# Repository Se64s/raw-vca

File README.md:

# raw-vca

Eurorack VCA module based in EDU DIY VCA from erica synths and Moritz Klein.

# About the project

This is the second module of the series 'RAW'.

The RAW concept is my way to ease access to the modular world, reducing the cost of the modules to the minimum and removing all unnecessary parts without scarify functionality.

In this case, I took the design of Moritz as a base for this VCA.

# Module overview

## Inputs

- 3 independent VCA.
- offset potentiometer per VCA.

## Output

### Square wave

### Triangle wave

### AR envelope

### Audio rate

## Calibration

Use the same procedure described for the Moritz VCA. Synth Diy Guy has an awesome video with the entire process.

- [Calibration](https://www.youtube.com/watch?v=xxr5fT-E7m0)

# Acknowledgments

All design and guts of this module were done by Moritz Klein so I recommend visiting his awesome videos to get a precise idea of how this module works.

- [mki x es.EDU](https://www.ericasynths.lv/news/edu-diy-vca/)

# Contact

Any feedback is welcome!
- Sebastián Del Moral - sebmorgal@gmail.com

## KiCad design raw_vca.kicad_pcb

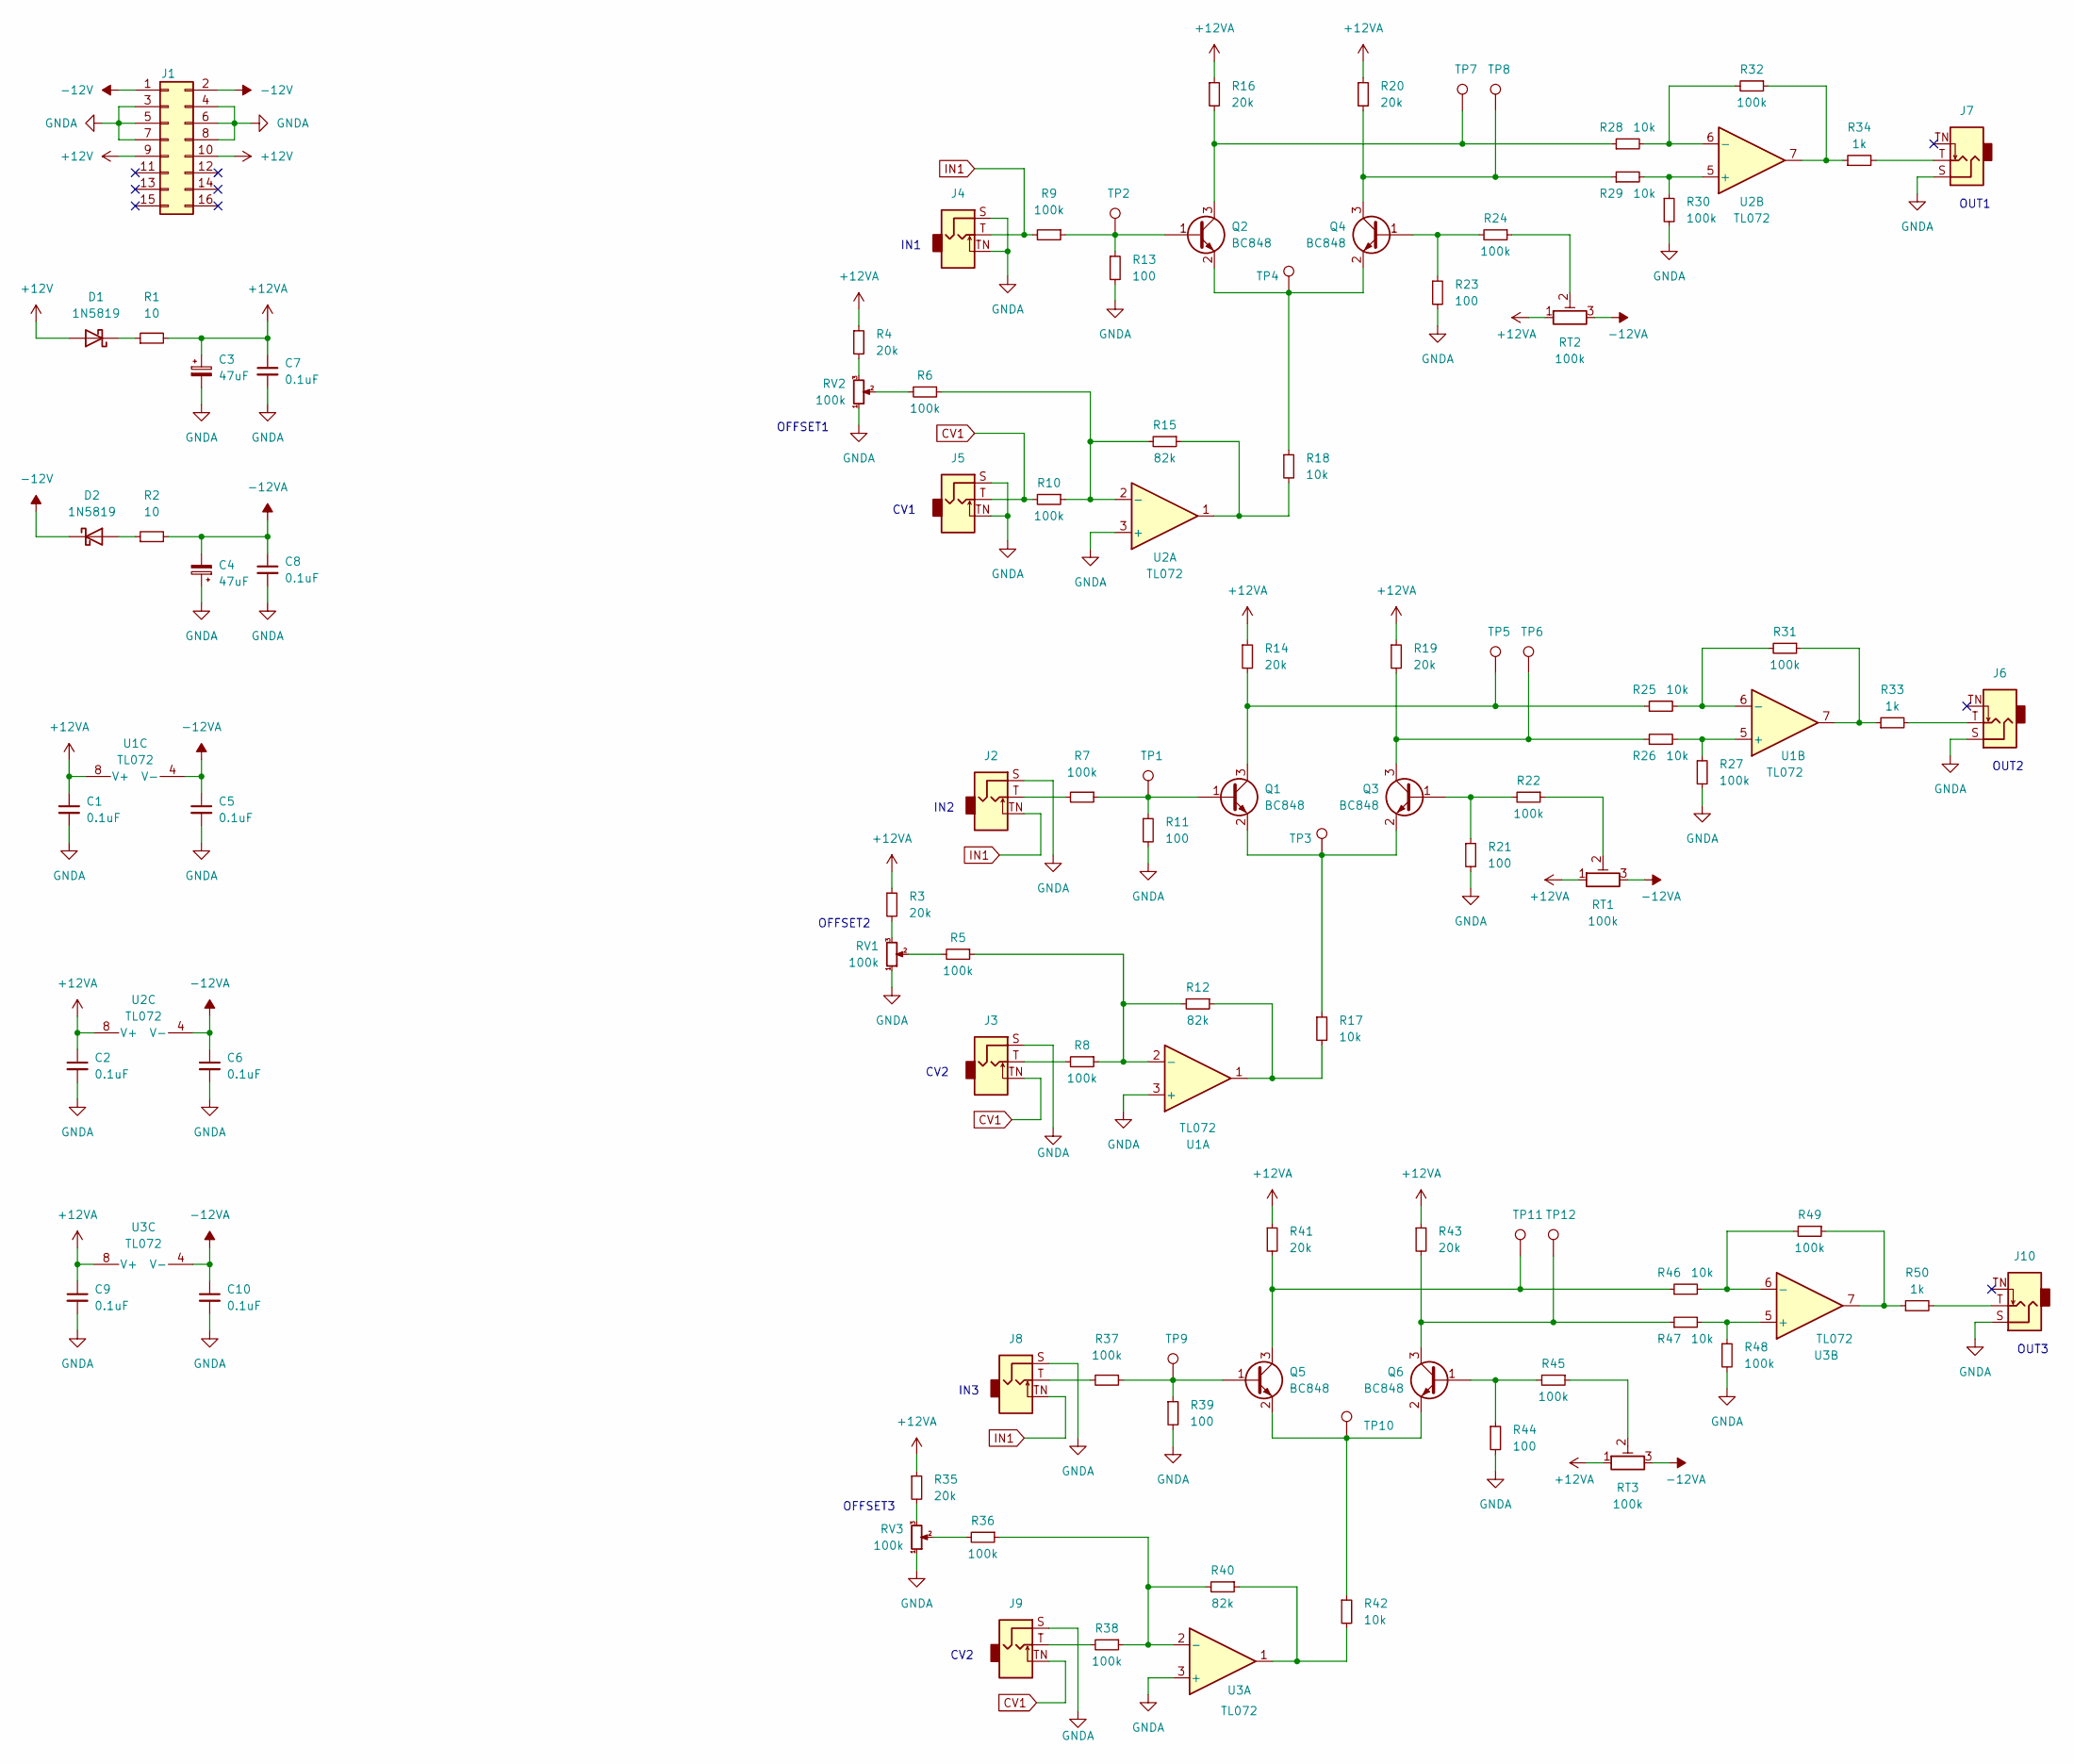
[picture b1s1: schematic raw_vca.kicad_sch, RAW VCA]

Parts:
C1, C2, C5, C6, C7, C8, C9, C10: 0.1uF; C_0603_1608Metric_Pad1.08x0.95mm_HandSolder
C3, C4: 47uF; CP_Elec_6.3x5.4
D1, D2: 1N5819; D_SOD-123
J1: Conn_02x08_Odd_Even; PinHeader_2x08_P2.54mm_Vertical_SMD
J2, J3, J4, J5, J6, J7, J8, J9, J10: AudioJack2_SwitchT; Jack_3.5mm_QingPu_WQP-PJ398SM_Vertical_CircularHoles
Q1, Q2, Q3, Q4, Q5, Q6: BC848; SOT-23
R1, R2: 10; R_0805_2012Metric_Pad1.20x1.40mm_HandSolder
R3, R4, R14, R16, R19, R20, R35, R41, R43: 20k; R_0603_1608Metric_Pad0.98x0.95mm_HandSolder
R5, R6, R7, R8, R9, R10, R22, R24, R27, R30, R31, R32, R36, R37, R38, R45, R48, R49: 100k; R_0603_1608Metric_Pad0.98x0.95mm_HandSolder
R11, R13, R21, R23, R39, R44: 100; R_0603_1608Metric_Pad0.98x0.95mm_HandSolder
R12, R15, R40: 82k; R_0603_1608Metric_Pad0.98x0.95mm_HandSolder
R17, R18, R25, R26, R28, R29, R42, R46, R47: 10k; R_0603_1608Metric_Pad0.98x0.95mm_HandSolder
R33, R34, R50: 1k; R_0603_1608Metric_Pad0.98x0.95mm_HandSolder
RT1, RT2, RT3: 100k; Potentiometer_Bourns_3296W_Vertical
RV1, RV2, RV3: 100k; Potentiometer_Alpha_RD901F-40-00D_Single_Vertical
TP1, TP2, TP3, TP4, TP5, TP6, TP7, TP8, TP9, TP10, TP11, TP12: TestPoint; TestPoint_Pad_D1.5mm
U1, U2, U3: TL072; SOIC-8_3.9x4.9mm_P1.27mm

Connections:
+12V: D1.2 (A), J1.9, J1.10
+12VA: C1.1, C2.1, C3.1, C7.1, C9.1, R1.2, R3.1, R4.1, R14.1, R16.1, R19.1, R20.1, R35.1, R41.1, R43.1, RT1.1, RT2.1, RT3.1, U1.8 (V+), U2.8 (V+), U3.8 (V+)
-12V: D2.1 (K), J1.1, J1.2
-12VA: C4.2, C5.1, C6.1, C8.1, C10.1, R2.2, RT1.3, RT2.3, RT3.3, U1.4 (V-), U2.4 (V-), U3.4 (V-)
CV1: J3.TN, J5.T, J9.TN, R10.2
GNDA: C1.2, C2.2, C3.2, C4.1, C5.2, C6.2, C7.2, C8.2, C9.2, C10.2, J1.3, J1.4, J1.5, J1.6, J1.7, J1.8, J2.S, J3.S, J4.S, J4.TN, J5.S, J5.TN, J6.S, J7.S, J8.S, J9.S, J10.S, R11.2, R13.2, R21.2, R23.2, R27.2, R30.2, R39.2, R44.2, R48.2, RV1.1, RV2.1, RV3.1, U1.3 (+), U2.3 (+), U3.3 (+)
IN1: J2.TN, J4.T, J8.TN, R9.2
unnamed: D1.1 (K), R1.1
unnamed: D2.2 (A), R2.1
unnamed: J2.T, R7.2
unnamed: J3.T, R8.2
unnamed: J6.T, R33.2
unnamed: J7.T, R34.2
unnamed: J8.T, R37.2
unnamed: J9.T, R38.2
unnamed: J10.T, R50.2
unnamed: Q1.1 (B), R7.1, R11.1, TP1.1
unnamed: Q1.2 (E), Q3.2 (E), R17.1, TP3.1
unnamed: Q1.3 (C), R14.2, R25.1, TP5.1
unnamed: Q2.1 (B), R9.1, R13.1, TP2.1
unnamed: Q2.2 (E), Q4.2 (E), R18.1, TP4.1
unnamed: Q2.3 (C), R16.2, R28.1, TP7.1
unnamed: Q3.1 (B), R21.1, R22.2
unnamed: Q3.3 (C), R19.2, R26.1, TP6.1
unnamed: Q4.1 (B), R23.1, R24.2
unnamed: Q4.3 (C), R20.2, R29.1, TP8.1
unnamed: Q5.1 (B), R37.1, R39.1, TP9.1
unnamed: Q5.2 (E), Q6.2 (E), R42.1, TP10.1
unnamed: Q5.3 (C), R41.2, R46.1, TP11.1
unnamed: Q6.1 (B), R44.1, R45.2
unnamed: Q6.3 (C), R43.2, R47.1, TP12.1
unnamed: R3.2, RV1.3
unnamed: R4.2, RV2.3
unnamed: R5.2, RV1.2
unnamed: R6.2, RV2.2
unnamed: R6.1, R10.1, R15.2, U2.2 (-)
unnamed: R12.1, R17.2, U1.1
unnamed: R5.1, R8.1, R12.2, U1.2 (-)
unnamed: R15.1, R18.2, U2.1
unnamed: R22.1, RT1.2
unnamed: R24.1, RT2.2
unnamed: R25.2, R31.2, U1.6 (-)
unnamed: R26.2, R27.1, U1.5 (+)
unnamed: R28.2, R32.2, U2.6 (-)
unnamed: R29.2, R30.1, U2.5 (+)
unnamed: R31.1, R33.1, U1.7
unnamed: R32.1, R34.1, U2.7
unnamed: R35.2, RV3.3
unnamed: R36.1, R38.1, R40.2, U3.2 (-)
unnamed: R36.2, RV3.2
unnamed: R40.1, R42.2, U3.1
unnamed: R45.1, RT3.2
unnamed: R46.2, R49.2, U3.6 (-)
unnamed: R47.2, R48.1, U3.5 (+)
unnamed: R49.1, R50.1, U3.7

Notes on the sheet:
OUT3
IN3
IN1
CV1
CV2
OFFSET3
OUT1
OFFSET1
IN2
OUT2
OFFSET2

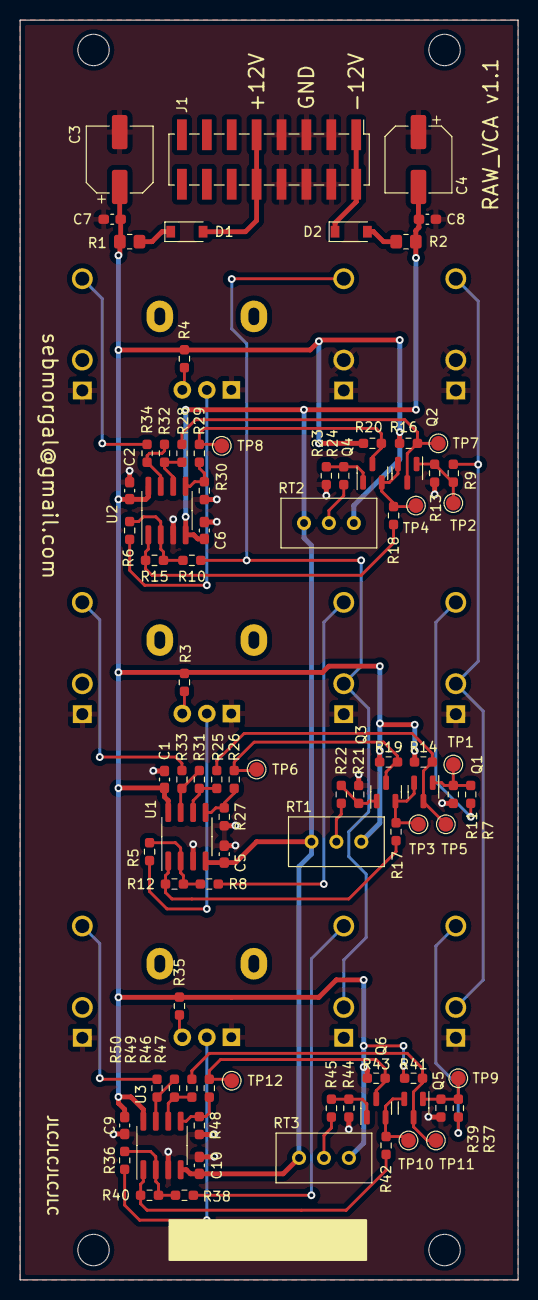
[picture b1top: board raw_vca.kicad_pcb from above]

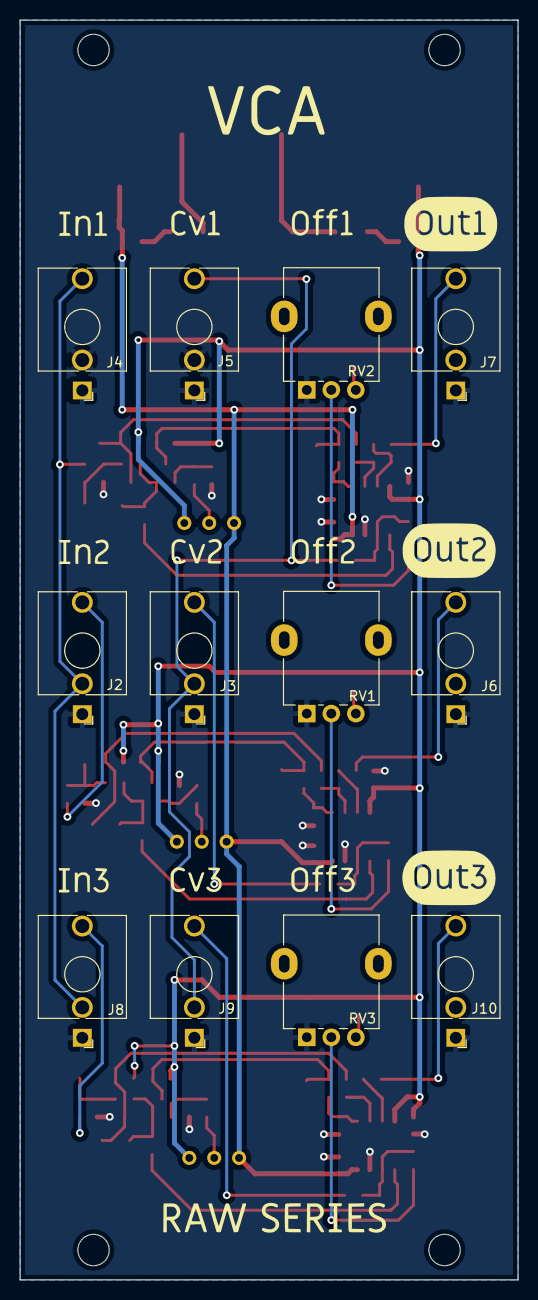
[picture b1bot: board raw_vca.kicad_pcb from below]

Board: 2 copper layers, 50.8 x 128.5 mm, 99 parts (12 on the bottom side), 55 nets.

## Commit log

2022-04-17 [MOD] Update git ignore and README file.
2022-04-17 [ADD] Commit with project files and fabrication outputs.
2022-04-22 feat: Add pics to readme
